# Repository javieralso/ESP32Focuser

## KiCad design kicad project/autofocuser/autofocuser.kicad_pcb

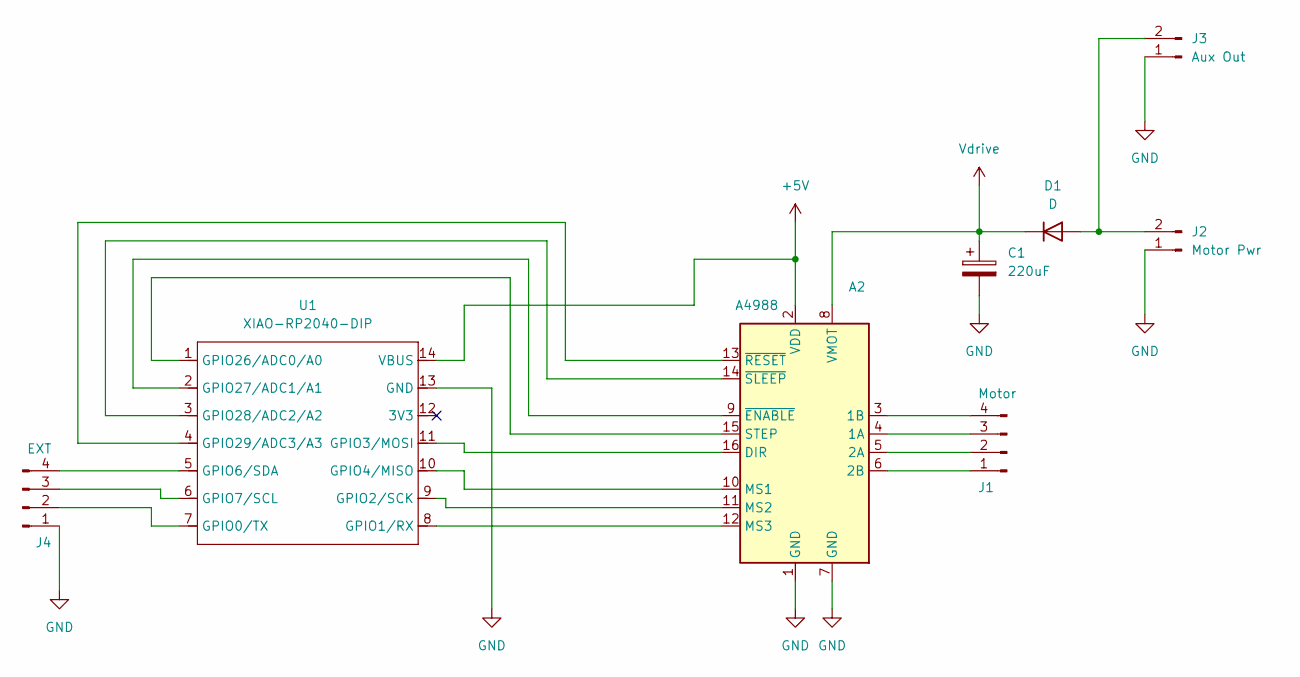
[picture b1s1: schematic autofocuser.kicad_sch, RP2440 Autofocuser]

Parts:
A2: A4988; Pololu_Breakout-16_15.2x20.3mm
C1: 220uF; CP_Elec_8x6.2
D1: D; D_SMC-RM10_Universal_Handsoldering
J1: Motor; PinHeader_1x04_P2.54mm_Vertical
J2: Motor Pwr; PinHeader_1x02_P2.54mm_Vertical
J3: Aux Out; PinHeader_1x02_P2.54mm_Vertical
J4: EXT; PinHeader_1x04_P2.54mm_Vertical
U1: XIAO-RP2040-DIP

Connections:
+5V: A2.2 (VDD), U1.14 (VBUS)
GND: A2.1 (GND), A2.7 (GND), C1.2, J2.1, J3.1, J4.1, U1.13 (GND)
unnamed: A2.4 (1A), J1.3
unnamed: A2.3 (1B), J1.4
unnamed: A2.5 (2A), J1.2
unnamed: A2.6 (2B), J1.1
unnamed: A2.16 (DIR), U1.11 (GPIO3/MOSI)
unnamed: A2.10 (MS1), U1.10 (GPIO4/MISO)
unnamed: A2.11 (MS2), U1.9 (GPIO2/SCK)
unnamed: A2.12 (MS3), U1.8 (GPIO1/RX)
unnamed: A2.15 (STEP), U1.1 (GPIO26/ADC0/A0)
unnamed: A2.9 (~ENABLE), U1.2 (GPIO27/ADC1/A1)
unnamed: A2.13 (~RESET), U1.4 (GPIO29/ADC3/A3)
unnamed: A2.14 (~SLEEP), U1.3 (GPIO28/ADC2/A2)
unnamed: D1.2 (A), J2.2, J3.2
unnamed: J4.2, U1.7 (GPIO0/TX)
unnamed: J4.3, U1.6 (GPIO7/SCL)
unnamed: J4.4, U1.5 (GPIO6/SDA)
Vdrive: A2.8 (VMOT), C1.1, D1.1 (K)

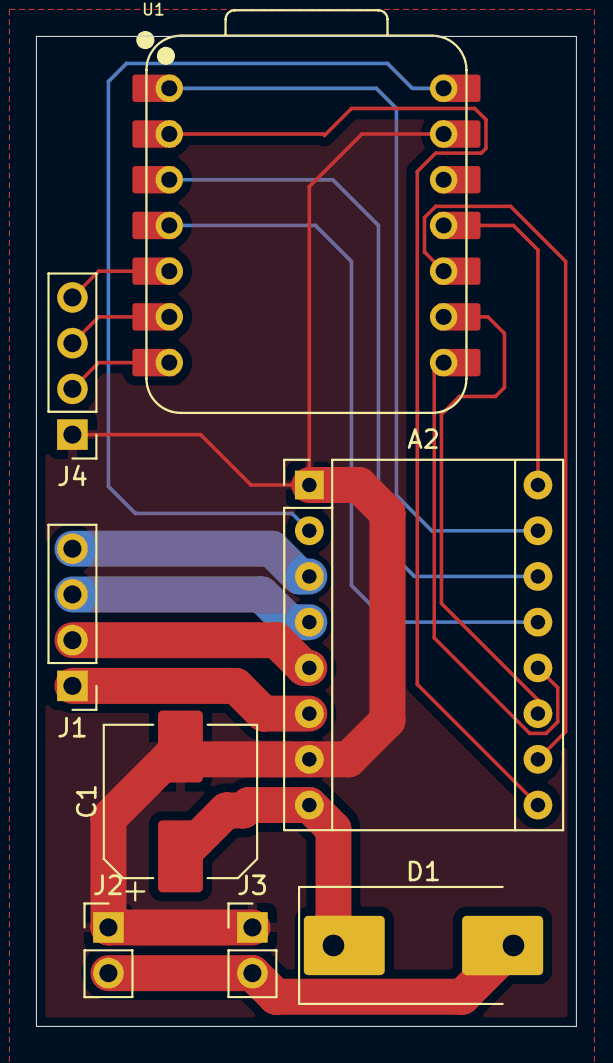
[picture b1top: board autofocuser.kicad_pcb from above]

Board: 2 copper layers, 30.0 x 55.0 mm, 8 parts (0 on the bottom side), 19 nets.

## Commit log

2024-06-01 local changes
2024-07-07 Add support for bluepill board and remove support for encoder
2024-07-07 Add kicad project
2025-04-21 Get rid of platformio folder-move to the root level
2025-05-11 Add FreeCad 3D model
2025-05-11 Remove old kicad project
2025-05-11 Reorganize FW files
2025-09-27 Add FreeCad Model
2025-09-27 Add back lid with support for the electronics
2025-11-30 Updating projects to new CAD versions
